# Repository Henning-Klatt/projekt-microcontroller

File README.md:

# project-microcontroller

[Adafruit ItsyBitsy nRF52840 Express Pinout](https://web.archive.org/web/20230508135748/https://cdn-learn.adafruit.com/assets/assets/000/110/600/original/adafruit_products_Adafruit_ItsyBitsy_nRF52840_pinout.png?1649279496)

[MicroPressure MPR Series Data Sheet](https://web.archive.org/web/20230522115035/https://prod-edam.honeywell.com/content/dam/honeywell-edam/sps/siot/en-us/products/sensors/pressure-sensors/board-mount-pressure-sensors/micropressure-mpr-series/documents/sps-siot-mpr-series-datasheet-32332628-ciid-172626.pdf?download=false)

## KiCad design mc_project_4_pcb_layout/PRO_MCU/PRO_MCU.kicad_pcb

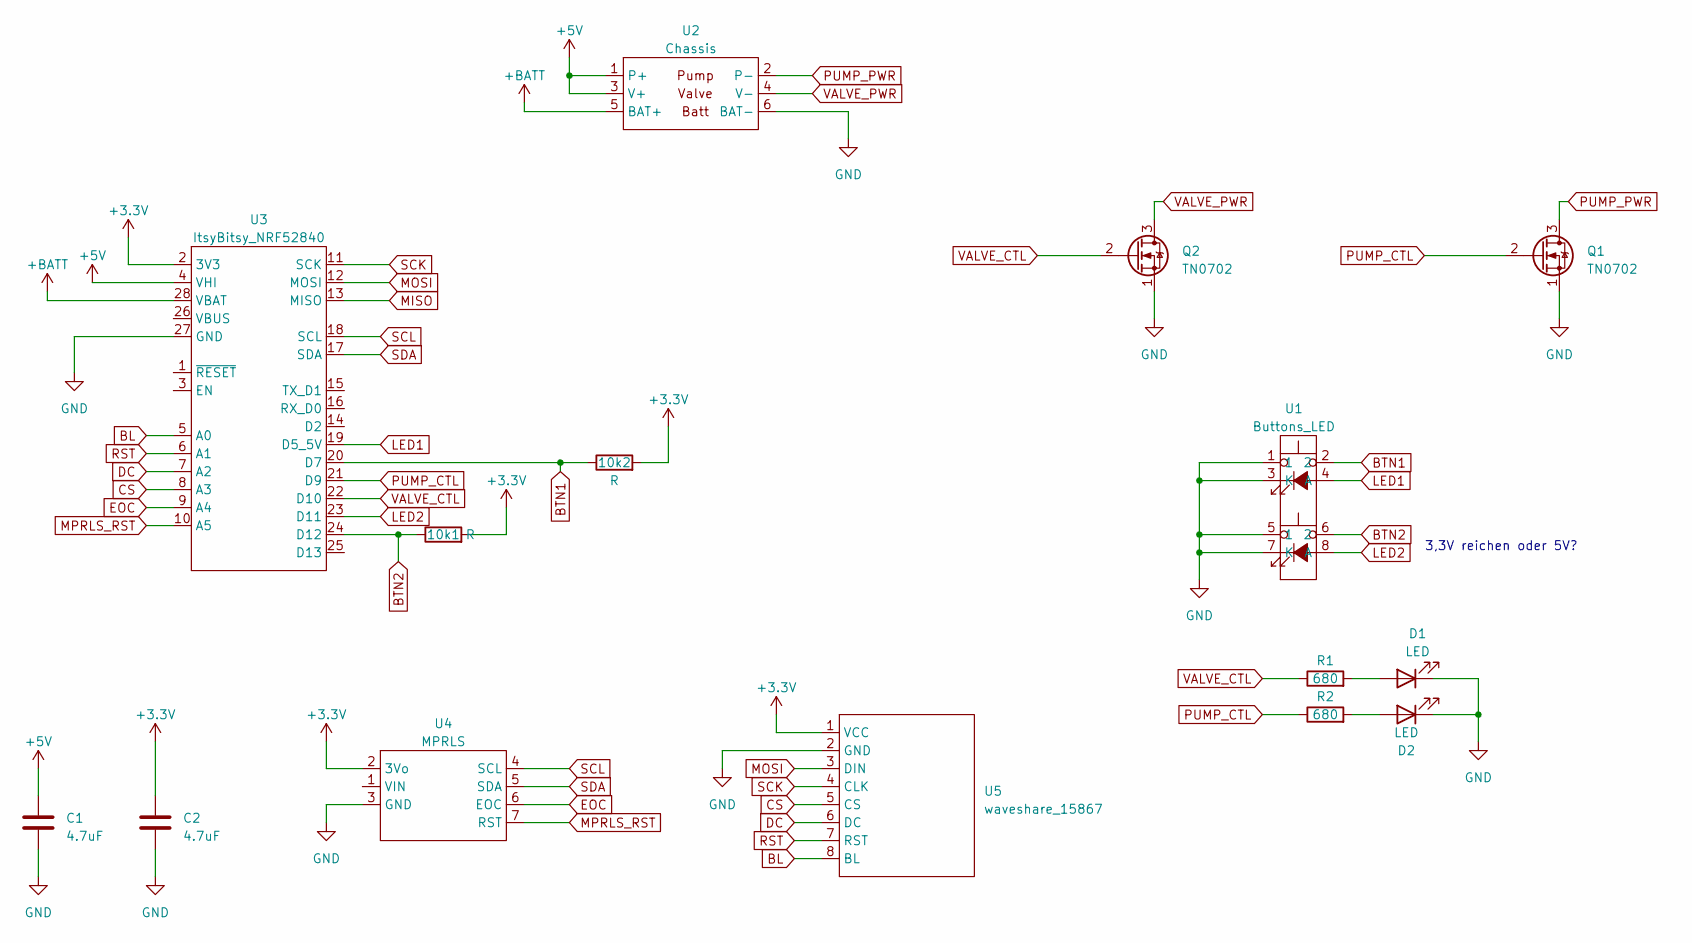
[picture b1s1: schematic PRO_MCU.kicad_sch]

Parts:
10k1, 10k2: R; R_Axial_DIN0207_L6.3mm_D2.5mm_P10.16mm_Horizontal
C1, C2: 4.7uF; C_0805_2012Metric
D1, D2: LED; LED_D3.0mm
Q1, Q2: TN0702; TO-92
R1, R2: 680; R_Axial_DIN0207_L6.3mm_D2.5mm_P10.16mm_Horizontal
U1: Buttons_LED; IDC-Header_2x04_P2.54mm_Vertical
U2: Chassis; IDC-Header_2x03_P2.54mm_Vertical
U3: ItsyBitsy_NRF52840
U4: MPRLS
U5: waveshare_15867; IDC-Header_2x04_P2.54mm_Vertical

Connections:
+3.3V: 10k1.2, 10k2.2, C2.1, U3.2 (3V3), U4.2 (3Vo), U5.1 (VCC)
+5V: C1.1, U2.1 (P+), U2.3 (V+), U3.4 (VHI)
+BATT: U2.5 (BAT+), U3.28 (VBAT)
BL: U3.5 (A0), U5.8 (BL)
BTN1: 10k2.1, U1.2, U3.20 (D7)
BTN2: 10k1.1, U1.6 (2), U3.24 (D12)
CS: U3.8 (A3), U5.5 (CS)
DC: U3.7 (A2), U5.6 (DC)
EOC: U3.9 (A4), U4.6 (EOC)
GND: C1.2, C2.2, D1.1 (K), D2.1 (K), Q1.1 (S), Q2.1 (S), U1.1, U1.3 (K), U1.5 (1), U1.7 (K), U2.6 (BAT-), U3.27 (GND), U4.3 (GND), U5.2 (GND)
LED1: U1.4 (A), U3.19 (D5_5V)
LED2: U1.8 (A), U3.23 (D11)
MISO: U3.13 (MISO)
MOSI: U3.12 (MOSI), U5.3 (DIN)
MPRLS_RST: U3.10 (A5), U4.7 (RST)
unnamed: D1.2 (A), R1.2
unnamed: D2.2 (A), R2.2
PUMP_CTL: Q1.2 (G), R2.1, U3.21 (D9)
PUMP_PWR: Q1.3 (D), U2.2 (P-)
RST: U3.6 (A1), U5.7 (RST)
SCK: U3.11 (SCK), U5.4 (CLK)
SCL: U3.18 (SCL), U4.4 (SCL)
SDA: U3.17 (SDA), U4.5 (SDA)
VALVE_CTL: Q2.2 (G), R1.1, U3.22 (D10)
VALVE_PWR: Q2.3 (D), U2.4 (V-)

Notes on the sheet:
3,3V reichen oder 5V?

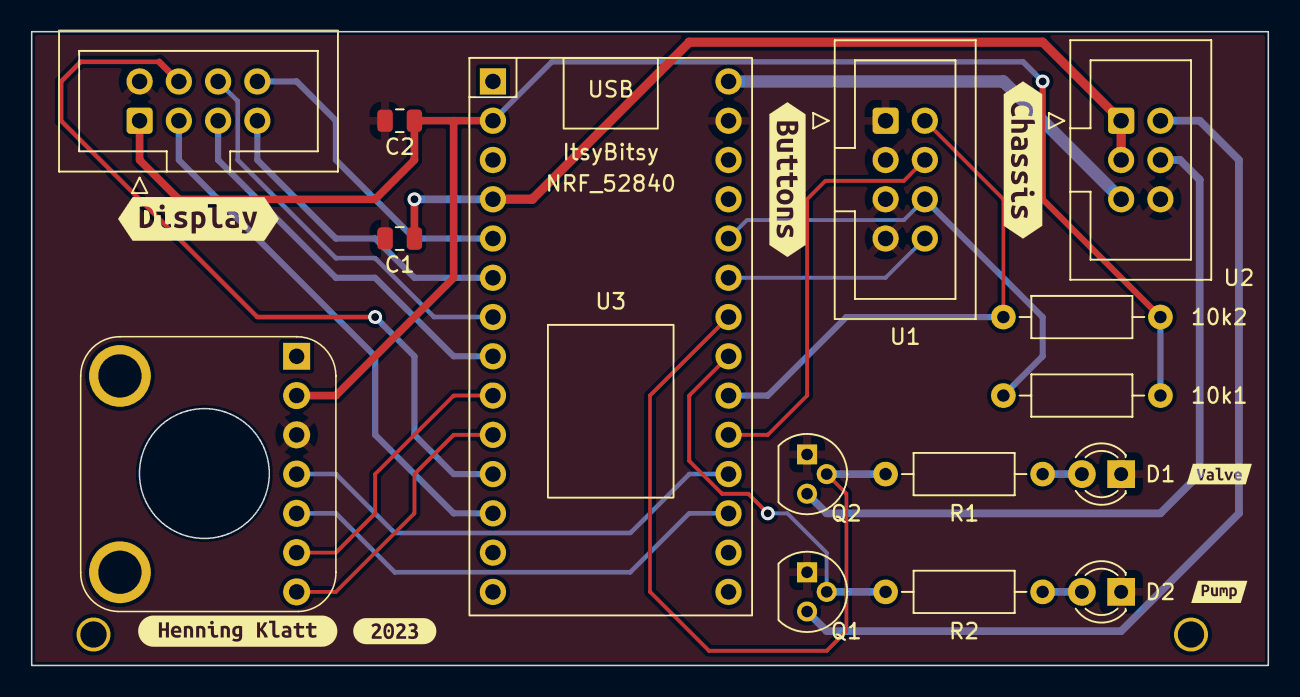
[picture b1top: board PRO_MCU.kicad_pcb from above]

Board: 2 copper layers, 80.0 x 41.0 mm, 23 parts (1 on the bottom side), 24 nets.

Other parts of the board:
Logo: BoardGeometry
kibuzzard-646250CA: G***; kibuzzard-646250CA
kibuzzard-646250F7: G***; kibuzzard-646250F7
kibuzzard-646251A1: G***; kibuzzard-646251A1
kibuzzard-646251AC: G***; kibuzzard-646251AC
kibuzzard-6462506E: G***; kibuzzard-6462506E
kibuzzard-64625088: G***; kibuzzard-64625088
kibuzzard-64625122: G***; kibuzzard-64625122

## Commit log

2023-04-18 first session
2023-04-24 Added schematic
2023-04-24 new led resistor value and supply voltage filter
2023-05-08 added Test code
2023-05-08 new pinout
2023-05-08 added README
2023-05-15 added pcb layout
2023-05-22 added project 5
2023-06-05 Added mc_project_6_libraries
2023-06-12 added project week 7
2023-06-19 Evalute not compiling
2023-06-25 last monday
2023-06-27 small progress
2023-07-10 filter not working
2023-07-10 first numbers coming in
2023-07-10 added diastolic filter
2023-07-10 diaPressure seems to work
